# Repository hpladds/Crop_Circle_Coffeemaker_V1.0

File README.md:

The code for the Ridiculous Coffee Machine  (AKA Crop Circle Coffeemaker) consists of python scripts that control the movement of the machinery and one a Bash script that calls the individual python scripts at the appropriate times.

A pair of python scripts control each motor: one script (with the "cw" designation) turns the motorshaft in a clockwise direction, the second script (with a ccw designation) turns the motorshaft in a counterclockwise direction.

For example: Script "1_cw.py" turns the shaft of motor 1 in a clockwise direction. Script "1_ccw.py" turns the motorshaft in a counterclockwise direction. 

From the Linux command line the following will rotate the motor's shaft at a rate of 1 step/millisecond for 10 steps:

$ python 1_cw.py 1 10

Each motor is fitted with a pulley gear wound with a cable. As the motorshaft rotates, the cable is either reeled in or out, and each motor works as a cable actuator. Three of these cable actuators are connected to central "effector" thereby creating a "Cable Robot."

The python script, "move_dist.py" coordinates the actions of the three stepper motors (the cable actuators) so as to control the movement of the "effector." Movement of the coffee cup is acheived by placing it upon the effector and executing the move_dist.py script.

Pouring water from the kettle is controlled with the Bash script "brew_flow.sh"  

"Brew.sh" is the script that initiates the brewing.

# Crop_Circle_Coffeemaker_V1.0

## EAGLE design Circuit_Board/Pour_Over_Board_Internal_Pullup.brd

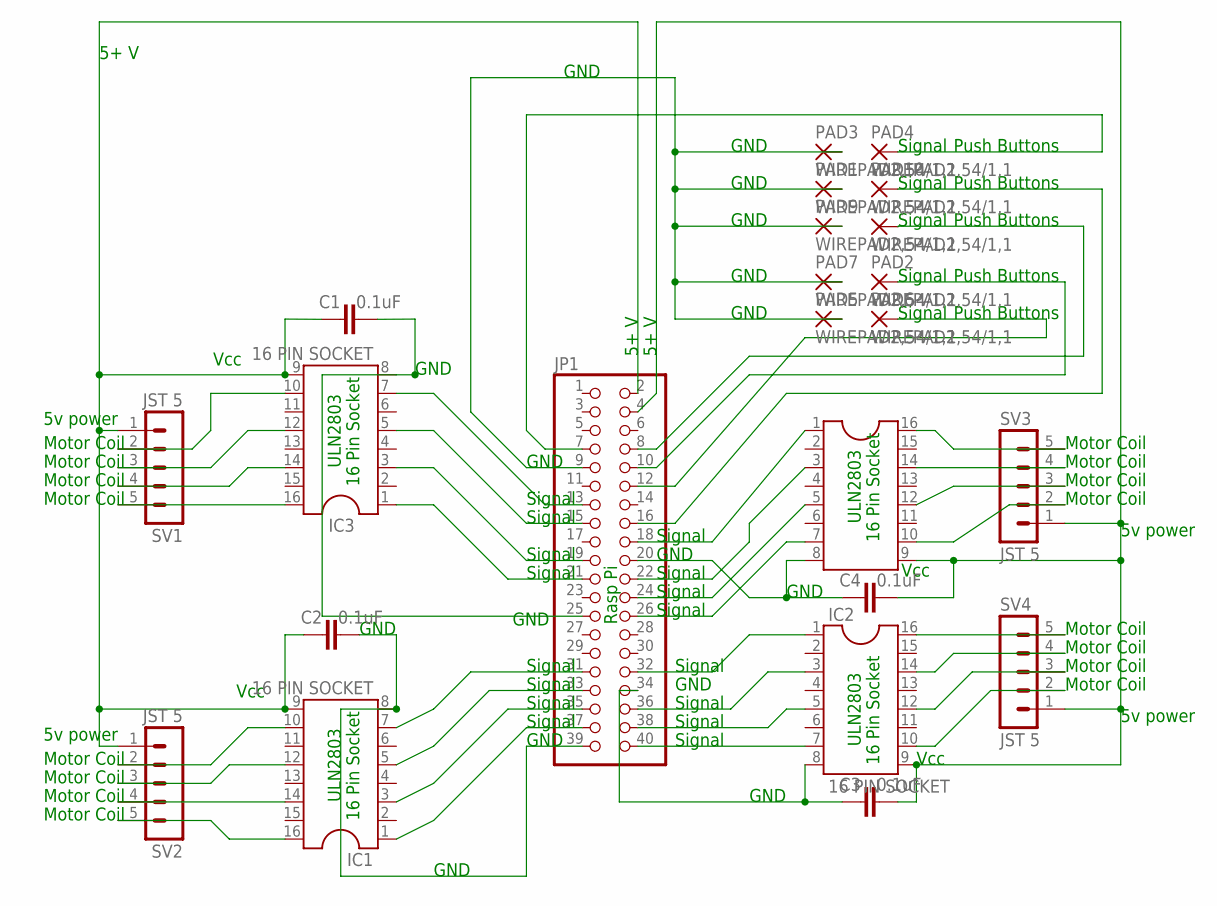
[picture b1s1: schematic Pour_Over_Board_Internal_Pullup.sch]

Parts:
C1, C2, C3, C4: 0.1uF; CAP-PTH-SMALL-KIT
IC1, IC2, IC3, IC4: 16 PIN SOCKET; SOCKET-16
JP1: RaspPiZero; 2X20
PAD1, PAD2, PAD3, PAD4, PAD5, PAD6, PAD7, PAD8, PAD9, PAD10: WIREPAD2,54/1,1; 2,54/1,1
SV1, SV2, SV3, SV4: JST 5; MA05-1

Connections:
unnamed: IC3.7, JP1.13
unnamed: C3.1, IC2.8, JP1.34
unnamed: JP1.12, PAD6.1
unnamed: C1.1, C2.1, IC1.9, IC3.9, JP1.2, SV1.1, SV2.1
unnamed: IC3.3, JP1.19
unnamed: IC3.1, JP1.21
unnamed: IC1.1, JP1.37
unnamed: IC1.3, JP1.35
unnamed: IC2.1, JP1.32
unnamed: IC2.3, JP1.36
unnamed: IC2.5, JP1.38
unnamed: IC2.7, JP1.40
unnamed: IC4.1, JP1.18
unnamed: IC4.3, JP1.22
unnamed: IC4.10, SV3.2
unnamed: IC4.12, SV3.3
unnamed: IC4.14, SV3.4
unnamed: IC4.16, SV3.5
unnamed: IC2.10, SV4.2
unnamed: IC2.12, SV4.3
unnamed: IC2.14, SV4.4
unnamed: IC2.16, SV4.5
unnamed: IC3.16, SV1.5
unnamed: JP1.16, PAD10.1
unnamed: IC3.14, SV1.4
unnamed: IC3.12, SV1.3
unnamed: IC4.5, JP1.24
unnamed: IC4.7, JP1.26
unnamed: IC1.5, JP1.33
unnamed: IC1.7, JP1.31
unnamed: IC3.10, SV1.2
unnamed: IC1.16, SV2.5
unnamed: IC1.14, SV2.4
unnamed: IC3.5, JP1.15
unnamed: C2.2, IC1.8, JP1.39
unnamed: IC1.12, SV2.3
unnamed: IC1.10, SV2.2
unnamed: C4.1, IC4.8, JP1.20
unnamed: C1.2, IC3.8, JP1.25
unnamed: C3.2, C4.2, IC2.9, IC4.9, JP1.4, SV3.1, SV4.1
unnamed: JP1.8, PAD8.1
unnamed: JP1.9, PAD1.1, PAD3.1, PAD5.1, PAD7.1, PAD9.1
unnamed: JP1.10, PAD2.1
unnamed: JP1.7, PAD4.1

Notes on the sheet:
5+ V
ULN2803
16 Pin Socket
5v power
Motor Coil
Signal
Rasp Pi
GND
Vcc
Push Buttons

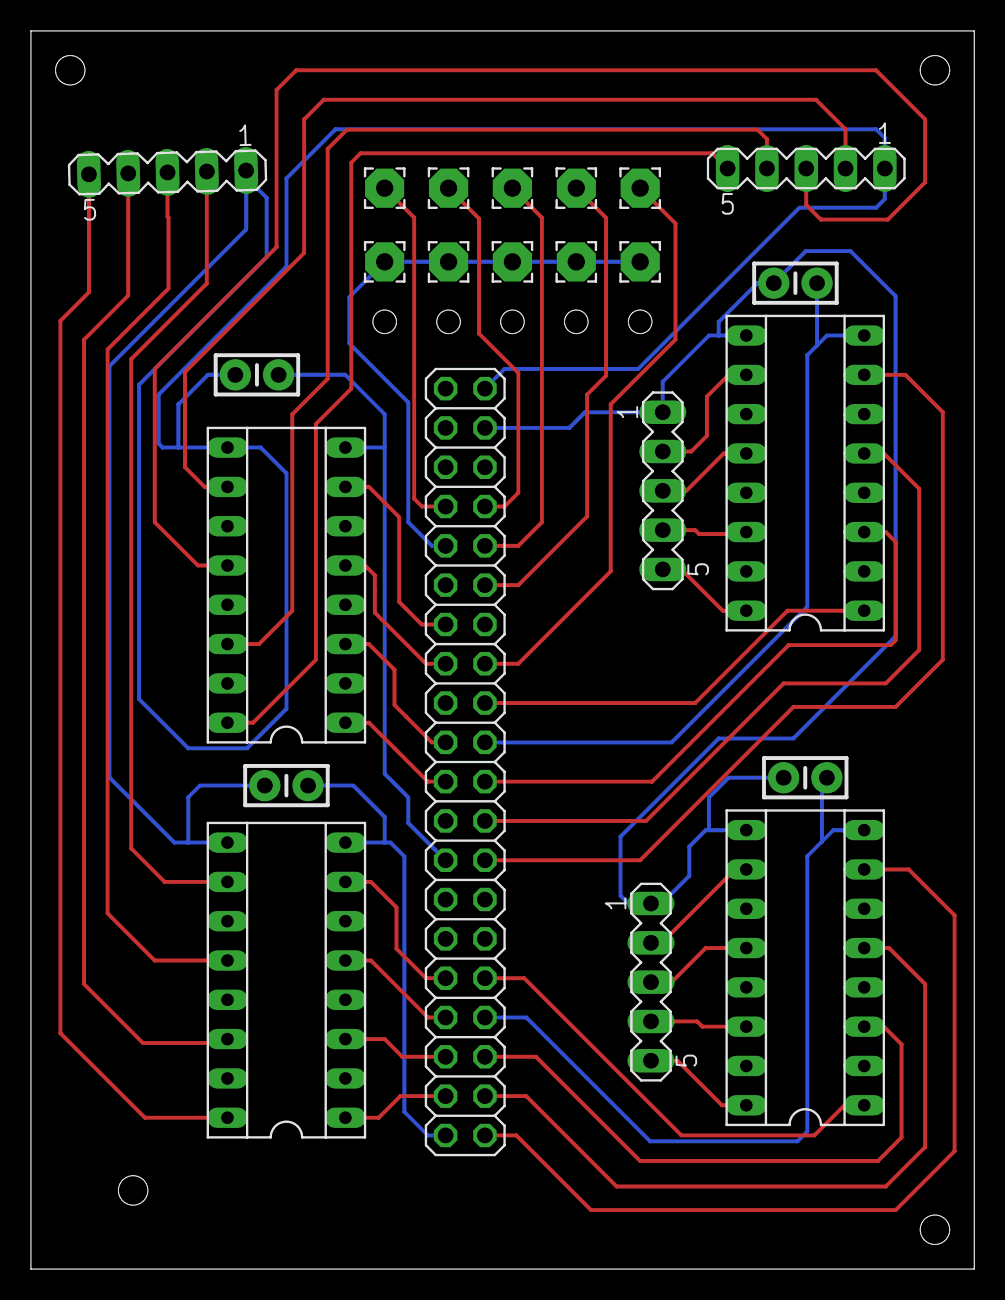
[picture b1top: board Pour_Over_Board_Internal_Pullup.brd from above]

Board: 2 copper layers, 61.0 x 80.0 mm, 23 parts (0 on the bottom side), 44 nets.

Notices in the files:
parts and their libraries:
SparkFun-Capacitors: Licensing: Creative Commons ShareAlike 4.0 International - https://creativecommons.org/licenses/by-sa/4.0
